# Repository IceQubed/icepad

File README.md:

# icepad

This is a 4 by 4 ortholinear keypad. It may be used as a numpad or macropad. It includes per-key LEDs and two potentiometer knobs.

## Prerequisites / Installation

This project was created using KiCad 5. 

The board is based around an STM32F042K6 microcontroller - code is available [here](https://github.com/IceQubed/icepad-sw).

## License

This work is licensed under a [Creative Commons Attribution-ShareAlike 4.0 International License](http://creativecommons.org/licenses/by-sa/4.0/).

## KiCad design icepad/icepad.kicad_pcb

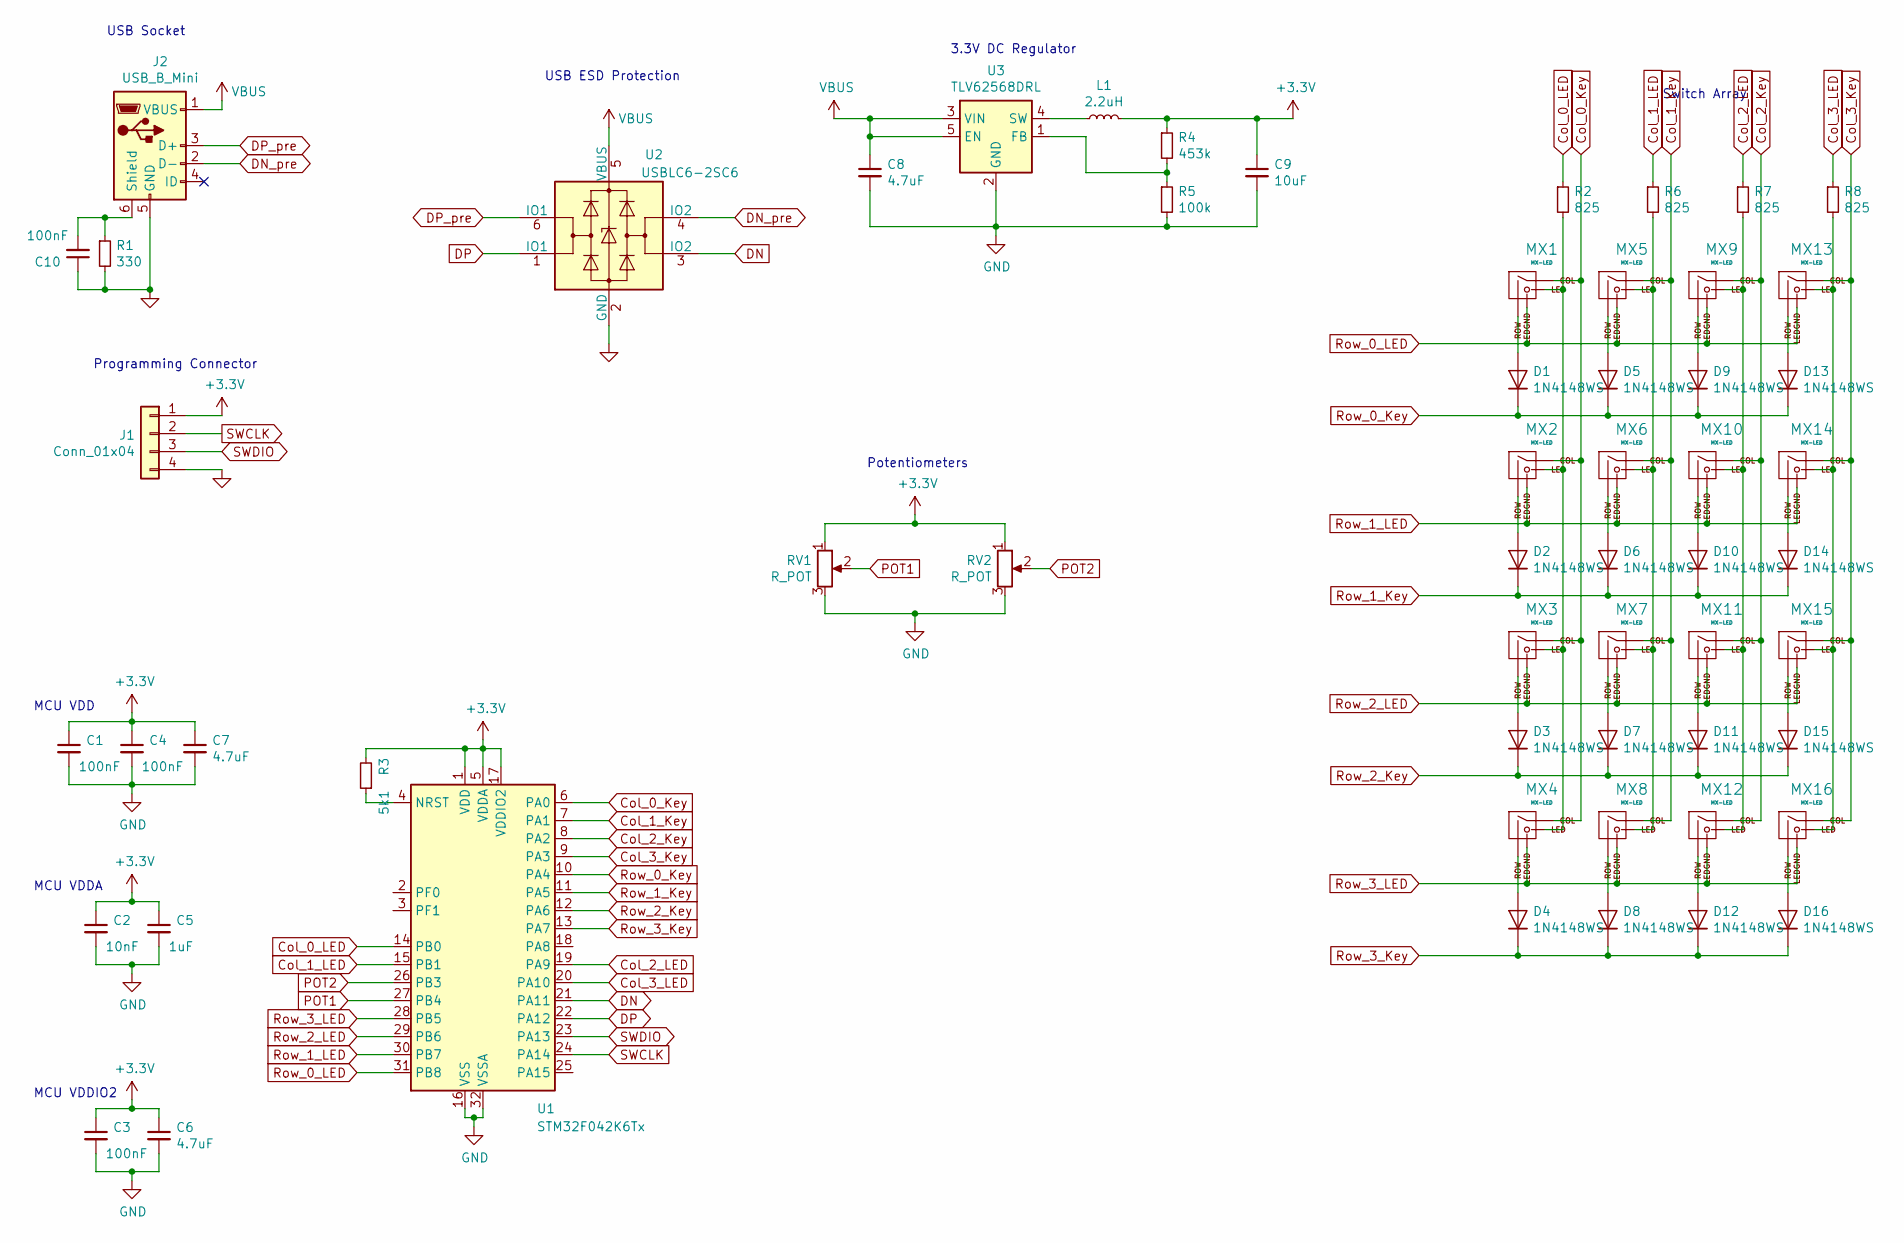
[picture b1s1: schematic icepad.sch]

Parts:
C1, C3, C4, C10: 100nF; C_0805_2012Metric; LCSC C49678
C2: 10nF; C_0805_2012Metric; LCSC C1710
C5: 1uF; C_0805_2012Metric; LCSC C28323
C6, C7, C8: 4.7uF; C_0805_2012Metric; LCSC C1779
C9: 10uF; C_0805_2012Metric; LCSC C15850
D1, D2, D3, D4, D5, D6, D7, D8, D9, D10, D11, D12, D13, D14, D15, D16: 1N4148WS; D_SOD-323; LCSC C2128
J1: Conn_01x04; PinHeader_1x04_P2.54mm_Horizontal
J2: USB_B_Mini; USB_Mini_B_Female_548190519
L1: 2.2uH; L_0805_2012Metric; LCSC C1043
MX1, MX2, MX3, MX4, MX5, MX6, MX7, MX8, MX9, MX10, MX11, MX12, MX13, MX14, MX15, MX16: MX-LED; MXOnly-1U
R1: 330; R_0805_2012Metric; LCSC C17630
R2, R6, R7, R8: 825; R_0805_2012Metric; LCSC C17839
R3: 5k1; R_0805_2012Metric; LCSC C27834
R4: 453k; R_0805_2012Metric; LCSC C17702
R5: 100k; R_0805_2012Metric; LCSC C17407
RV1, RV2: R_POT; RK09K1130A5R
U1: STM32F042K6Tx; LQFP-32_7x7mm_P0.8mm; LCSC C69216
U2: USBLC6-2SC6; SOT-23-6; LCSC C7519
U3: TLV62568DRL; SOT-563; LCSC C398370

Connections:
+3V3: C1.1, C2.1, C3.1, C4.1, C5.1, C6.1, C7.1, C9.1, J1.1, L1.2, R3.2, R4.1, RV1.1, RV2.1, U1.1 (VDD), U1.5 (VDDA), U1.17 (VDDIO2)
Col_0_Key: MX1.1 (COL), MX2.1 (COL), MX3.1 (COL), MX4.1 (COL), U1.6 (PA0)
Col_0_LED: R2.1, U1.14 (PB0)
Col_1_Key: MX5.1 (COL), MX6.1 (COL), MX7.1 (COL), MX8.1 (COL), U1.7 (PA1)
Col_1_LED: R6.1, U1.15 (PB1)
Col_2_Key: MX9.1 (COL), MX10.1 (COL), MX11.1 (COL), MX12.1 (COL), U1.8 (PA2)
Col_2_LED: R7.1, U1.19 (PA9)
Col_3_Key: MX13.1 (COL), MX14.1 (COL), MX15.1 (COL), MX16.1 (COL), U1.9 (PA3)
Col_3_LED: R8.1, U1.20 (PA10)
DN: U1.21 (PA11), U2.3 (IO2)
DN_pre: J2.2 (D-), U2.4 (IO2)
DP: U1.22 (PA12), U2.1 (IO1)
DP_pre: J2.3 (D+), U2.6 (IO1)
GND: C1.2, C2.2, C3.2, C4.2, C5.2, C6.2, C7.2, C8.2, C9.2, C10.1, J1.4, J2.5 (GND), R1.2, R5.2, RV1.3, RV2.3, U1.16 (VSS), U1.32 (VSSA), U2.2 (GND), U3.2 (GND)
unnamed: C10.2, J2.6 (Shield), R1.1
unnamed: D1.2 (A), MX1.2 (ROW)
unnamed: D2.2 (A), MX2.2 (ROW)
unnamed: D3.2 (A), MX3.2 (ROW)
unnamed: D4.2 (A), MX4.2 (ROW)
unnamed: D5.2 (A), MX5.2 (ROW)
unnamed: D6.2 (A), MX6.2 (ROW)
unnamed: D7.2 (A), MX7.2 (ROW)
unnamed: D8.2 (A), MX8.2 (ROW)
unnamed: D9.2 (A), MX9.2 (ROW)
unnamed: D10.2 (A), MX10.2 (ROW)
unnamed: D11.2 (A), MX11.2 (ROW)
unnamed: D12.2 (A), MX12.2 (ROW)
unnamed: D13.2 (A), MX13.2 (ROW)
unnamed: D14.2 (A), MX14.2 (ROW)
unnamed: D15.2 (A), MX15.2 (ROW)
unnamed: D16.2 (A), MX16.2 (ROW)
unnamed: L1.1, U3.4 (SW)
unnamed: MX1.3 (LED), MX2.3 (LED), MX3.3 (LED), MX4.3 (LED), R2.2
unnamed: MX5.3 (LED), MX6.3 (LED), MX7.3 (LED), MX8.3 (LED), R6.2
unnamed: MX9.3 (LED), MX10.3 (LED), MX11.3 (LED), MX12.3 (LED), R7.2
unnamed: MX13.3 (LED), MX14.3 (LED), MX15.3 (LED), MX16.3 (LED), R8.2
unnamed: R3.1, U1.4 (NRST)
unnamed: R4.2, R5.1, U3.1 (FB)
POT1: RV1.2, U1.27 (PB4)
POT2: RV2.2, U1.26 (PB3)
Row_0_Key: D1.1 (K), D5.1 (K), D9.1 (K), D13.1 (K), U1.10 (PA4)
Row_0_LED: MX1.4 (LEDGND), MX5.4 (LEDGND), MX9.4 (LEDGND), MX13.4 (LEDGND), U1.31 (PB8)
Row_1_Key: D2.1 (K), D6.1 (K), D10.1 (K), D14.1 (K), U1.11 (PA5)
Row_1_LED: MX2.4 (LEDGND), MX6.4 (LEDGND), MX10.4 (LEDGND), MX14.4 (LEDGND), U1.30 (PB7)
Row_2_Key: D3.1 (K), D7.1 (K), D11.1 (K), D15.1 (K), U1.12 (PA6)
Row_2_LED: MX3.4 (LEDGND), MX7.4 (LEDGND), MX11.4 (LEDGND), MX15.4 (LEDGND), U1.29 (PB6)
Row_3_Key: D4.1 (K), D8.1 (K), D12.1 (K), D16.1 (K), U1.13 (PA7)
Row_3_LED: MX4.4 (LEDGND), MX8.4 (LEDGND), MX12.4 (LEDGND), MX16.4 (LEDGND), U1.28 (PB5)
SWCLK: J1.2, U1.24 (PA14)
SWDIO: J1.3, U1.23 (PA13)
VBUS: C8.1, J2.1 (VBUS), U2.5 (VBUS), U3.3 (VIN), U3.5 (EN)

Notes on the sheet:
USB ESD Protection
USB Socket
3.3V DC Regulator
Switch Array
MCU VDD
MCU VDDA
MCU VDDIO2
Programming Connector
Potentiometers

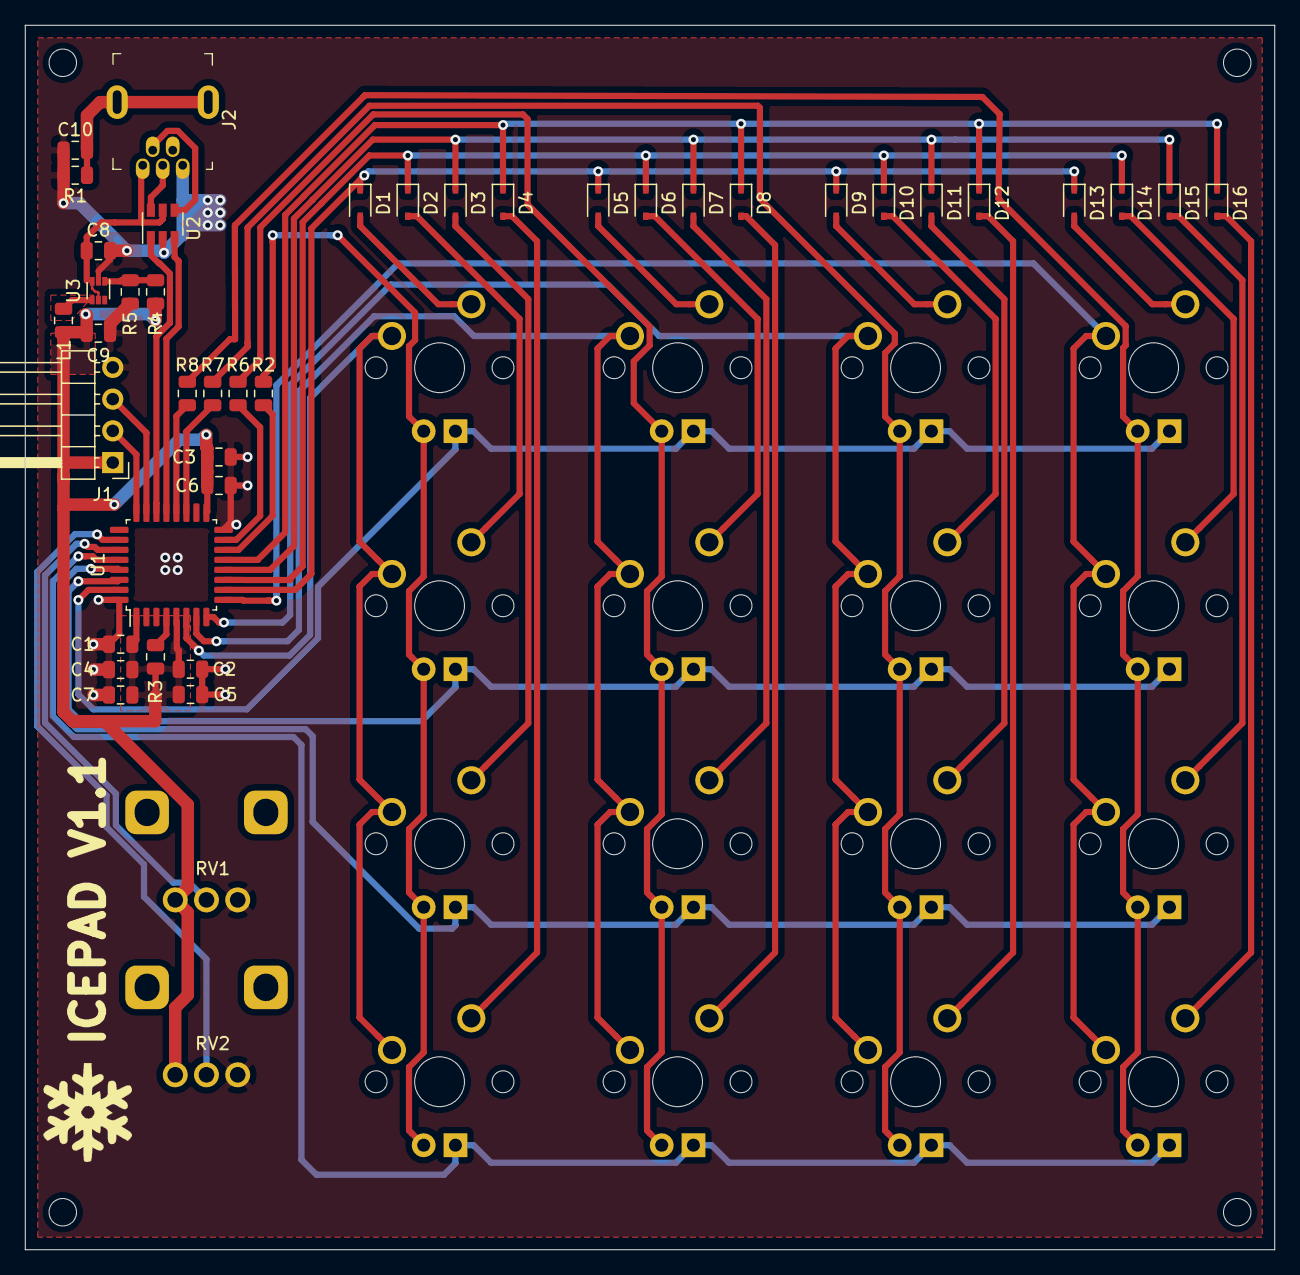
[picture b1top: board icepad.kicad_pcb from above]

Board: 2 copper layers, 100.0 x 98.0 mm, 62 parts (0 on the bottom side), 51 nets.

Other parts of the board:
MNT: MountingHole_2.2mm_M2
MNT#2, MNT#3, MNT#4: MountingHole_2.2mm_M2

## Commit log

2020-02-06 added keyswitch submodule
2020-02-06 initialised kicad project folder
2020-02-06 wired up switch matrix
2020-02-06 added mcu
2020-02-06 removed old submodule
2020-02-06 added usb c connector
2020-02-06 schematic edits
2020-02-08 Added DC DC converter and decoupling caps for MCU
2020-02-08 added NC pins
2020-02-08 Added PCB footprint and associated schematic to footprints
2020-02-10 set up key grid on PCB layout
2020-02-10 routed MCU and connector
2020-02-10 completed routing without led
2020-04-22 added jlcpcb stock and new pcb design
2020-04-22 complete new pcba design
2020-04-23 Completed routing, added LED resistors
2020-04-23 added potentiometers and 3d models
2020-04-23 changed potentiometer
2020-05-03 as sent for production
